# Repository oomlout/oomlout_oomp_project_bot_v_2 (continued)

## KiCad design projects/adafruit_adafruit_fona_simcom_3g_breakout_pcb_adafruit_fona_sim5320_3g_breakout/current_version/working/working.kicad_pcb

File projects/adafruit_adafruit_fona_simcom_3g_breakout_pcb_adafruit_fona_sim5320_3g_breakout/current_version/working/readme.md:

# adafruit_fona_simcom_3g_breakout_pcb
 
## summary 
* id: adafruit_adafruit_fona_simcom_3g_breakout_pcb_adafruit_fona_sim5320_3g_breakout
* user: adafruit
* name: adafruit_fona_simcom_3g_breakout_pcb
* board: adafruit_fona_sim5320_3g_breakout
* repo: https://github.com/adafruit/Adafruit-FONA-SIMCOM-3G-Breakout-PCB

* src_file_repo_sch: 
* src_file_repo_sch_link: https://github.com/adafruit/Adafruit-FONA-SIMCOM-3G-Breakout-PCB/tree/master/
* full details link: https://github.com/oomlout/oomlout_oomp_project_bot_v_2/tree/main/projects/adafruit_adafruit_fona_simcom_3g_breakout_pcb_adafruit_fona_sim5320_3g_breakout/current_version/working  

## schematic  
  
[schematic (pdf)](working_schematic.pdf) 

## pcb  

[board (pdf)](working.pdf)  

## working_bom
| Id | Designator | Footprint | Quantity | Designation | Supplier and ref |  | None | 
| --- | --- | --- | --- | --- | --- | --- | --- | 
| 1 | R2,R4,R5 | 0805-NO | 3 | 1K |  |  | [''] | 
| 2 | C15,C17 | RESPACK_4X0603 | 2 | 10pF |  |  | [''] | 
| 3 | IC1 | TSSOP14 | 1 | 74VHCT125PW |  |  | [''] | 
| 4 | D2 | SOT363 | 1 | SMF05C |  |  | [''] | 
| 5 | FID1,FID2,FID3,FID4,FID5 | FIDUCIAL_1MM | 5 | FIDUCIAL" |  |  | [''] | 
| 6 | U2 | SOT23-5 | 1 | MCP73831T-2ACI/OT |  |  | [''] | 
| 7 | Q2 | SOT23-WIDE | 1 | bss138 |  |  | [''] | 
| 8 | C14,C16 | RESPACK_4X0603 | 2 | 33pF |  |  | [''] | 
| 9 | D4,D5,D6,D3 | SOD-323 | 4 | 1N4148 |  |  | [''] | 
| 10 | C9,C11 | 0805-NO | 2 | 10uF |  |  | [''] | 
| 11 | R6,R3 | 0805-NO | 2 | 2K |  |  | [''] | 
| 12 | CHRG0 | CHIPLED_0805_NOOUTLINE | 1 | ORANGE |  |  | [''] | 
| 13 | JP1 | 1X18_ROUND70 | 1 |  |  |  | [''] | 
| 14 | GPSBIAS0 | SOLDERJUMPER_ARROW_NOPASTE | 1 |  |  |  | [''] | 
| 15 | CN2 | JSTPH2 | 1 | JSTPH |  |  | [''] | 
| 16 | C6,C4,C10,C3 | 0805-NO | 4 | 33pF |  |  | [''] | 
| 17 | C1 | 0805-NO | 1 | 10ÂµF |  |  | [''] | 
| 18 | C8,C5 | 0805-NO | 2 | 10pF |  |  | [''] | 
| 19 | X1 | SMA_EDGELAUNCH_UFL | 1 | uFL |  |  | [''] | 
| 20 | U$33,U$34 | MOUNTINGHOLE_2.5_PLATED | 2 | MOUNTINGHOLE2.5 |  |  | [''] | 
| 21 | U$21 | ADAFRUIT_2.5MM | 1 |  |  |  | [''] | 
| 22 | R1 | 0805-NO | 1 | 470 |  |  | [''] | 
| 23 | C2,C7 | C1210 | 2 | 100uF |  |  | [''] | 
| 24 | PWRSTAT0,DONE0 | CHIPLED_0805_NOOUTLINE | 2 | GREEN |  |  | [''] | 
| 25 | U1 | SIM5320 | 1 | SIM5320 |  |  | [''] | 
| 26 | X2 | 4UCONN_20329 | 1 | MicroB |  |  | [''] | 
| 27 | R8 | 0805-NO | 1 | 10K |  |  | [''] | 
| 28 | L2 | _0805MP | 1 | 33nH |  |  | [''] | 
| 29 | X3 | U.FL | 1 | uFL |  |  | [''] | 
| 30 | NETSTAT0 | CHIPLED_0805_NOOUTLINE | 1 | RED |  |  | [''] | 
| 31 | JP2 | 1X02_ROUND | 1 |  |  |  | [''] | 
| 32 | X4 | 4UCONN_18510 | 1 | 4UCONN_18510 |  |  | [''] | 
| 33 | D1 | SOD-123 | 1 | MMSZ5231BT1G |  |  | [''] | 
| 34 | SW1 | BTN_KMR2_4.6X2.8 | 1 | KMR2 |  |  | [''] | 
| 35 | U$42 | ADAFRUIT_TEXT_20MM | 1 |  |  |  | [''] | 
| 36 | U$25 | PCBFEAT-REV-040 | 1 |  |  |  | [''] | 
| 37 | TP1 | TP11R | 1 | TPTP11R |  |  | [''] | 
| 38 | U$36 | ADAFRUIT_5MM | 1 |  |  |  | [''] | 
| 39 | X6 | C707_10M006_512_2 | 1 | SIM_LOCKAMPHENOL |  |  | [''] | 
| 40 | U$26 | FONA_LOGO | 1 |  |  |  | [''] | 

## bom_schematic
| Ref | Qnty | Value | Cmp name | Footprint | Description | Vendor | DNP | 
| --- | --- | --- | --- | --- | --- | --- | --- | 
| C1 | 1 | 10ÂµF | CAP_CERAMIC0805-NOOUTLINE | working:0805-NO |  |  |  | 
| C2, C7 | 2 | 100uF | C-USC1210 | working:C1210 |  |  |  | 
| C3, C4, C6, C10 | 4 | 33pF | CAP_CERAMIC0805-NOOUTLINE | working:0805-NO |  |  |  | 
| C5, C8 | 2 | 10pF | CAP_CERAMIC0805-NOOUTLINE | working:0805-NO |  |  |  | 
| C9, C11 | 2 | 10uF | CAP_CERAMIC0805-NOOUTLINE | working:0805-NO |  |  |  | 
| C14, C16 | 2 | 33pF | CAP_4PACK1206 | working:RESPACK_4X0603 |  |  |  | 
| C15, C17 | 2 | 10pF | CAP_4PACK1206 | working:RESPACK_4X0603 |  |  |  | 
| CHRG0 | 1 | ORANGE | LED0805_NOOUTLINE | working:CHIPLED_0805_NOOUTLINE |  |  |  | 
| CN2 | 1 | JSTPH | JST_2PIN | working:JSTPH2 |  |  |  | 
| D1 | 1 | MMSZ5231BT1G | DIODE-ZENERSOD123 | working:SOD-123 |  |  |  | 
| D2 | 1 | SMF05C | TVSARRAY_5LANE | working:SOT363 |  |  |  | 
| D3, D4, D5, D6 | 4 | 1N4148 | DIODESOD-323 | working:SOD-323 |  |  |  | 
| DONE0 | 1 | GREEN | LED0805_NOOUTLINE | working:CHIPLED_0805_NOOUTLINE |  |  |  | 
| FID1, FID2, FID3, FID4, FID5 | 5 | FIDUCIAL"" | FIDUCIAL{dblquote}{dblquote} | working:FIDUCIAL_1MM |  |  |  | 
| GPSBIAS0 | 1 | SOLDERJUMPER | SOLDERJUMPER | working:SOLDERJUMPER_ARROW_NOPASTE |  |  |  | 
| IC1 | 1 | 74125PW | 74125PW | working:TSSOP14 |  |  |  | 
| JP1 | 1 | HEADER-1X18 | HEADER-1X18 | working:1X18_ROUND70 |  |  |  | 
| JP2 | 1 | HEADER-1X2ROUND | HEADER-1X2ROUND | working:1X02_ROUND |  |  |  | 
| L2 | 1 | 33nH | INDUCTOR_0805MP | working:_0805MP |  |  |  | 
| NETSTAT0 | 1 | RED | LED0805_NOOUTLINE | working:CHIPLED_0805_NOOUTLINE |  |  |  | 
| PWRSTAT0 | 1 | GREEN | LED0805_NOOUTLINE | working:CHIPLED_0805_NOOUTLINE |  |  |  | 
| Q2 | 1 | bss138 | MOSFET-NWIDE | working:SOT23-WIDE |  |  |  | 
| R1 | 1 | 470 | RESISTOR0805_NOOUTLINE | working:0805-NO |  |  |  | 
| R2, R4, R5 | 3 | 1K | RESISTOR0805_NOOUTLINE | working:0805-NO |  |  |  | 
| R3, R6 | 2 | 2K | RESISTOR0805_NOOUTLINE | working:0805-NO |  |  |  | 
| R8 | 1 | 10K | RESISTOR0805_NOOUTLINE | working:0805-NO |  |  |  | 
| SW1 | 1 | KMR2 | SWITCH_TACT_SMT4.6X2.8 | working:BTN_KMR2_4.6X2.8 |  |  |  | 
| TP1 | 1 | TPTP11R | TPTP11R | working:TP11R |  |  |  | 
| U1 | 1 | SIM5320 | GSM_SIM5320_LITERAL | working:SIM5320 |  |  |  | 
| U2 | 1 | MCP73831T-2ACI/OT | MCP73831/2 | working:SOT23-5 |  |  |  | 
| U$33, U$34 | 2 | MOUNTINGHOLE2.5 | MOUNTINGHOLE2.5 | working:MOUNTINGHOLE_2.5_PLATED |  |  |  | 
| X1 | 1 | uFL | SMACONNECTOR_EDGE_UFL | working:SMA_EDGELAUNCH_UFL |  |  |  | 
| X2 | 1 | MicroB | USBMICRO_20329 | working:4UCONN_20329 |  |  |  | 
| X3 | 1 | uFL | ANTENNA_U.FL | working:U.FL |  |  |  | 
| X4 | 1 | 4UCONN_18510 | AUDIO_3.5MMJACK_4POL | working:4UCONN_18510 |  |  |  | 
| X6 | 1 | SIM_LOCKAMPHENOL | SIM_LOCKAMPHENOL | working:C707_10M006_512_2 |  |  |  | 

## mounting_holes
| x | y | package | value | ref | size | 
| --- | --- | --- | --- | --- | --- | 
| 40.64 | 0.0 | MOUNTINGHOLE_2.5_PLATED | MOUNTINGHOLE2.5 | U$33 | m3 | 
| 0.0 | 0.0 | MOUNTINGHOLE_2.5_PLATED | MOUNTINGHOLE2.5 | U$34 | m3 |

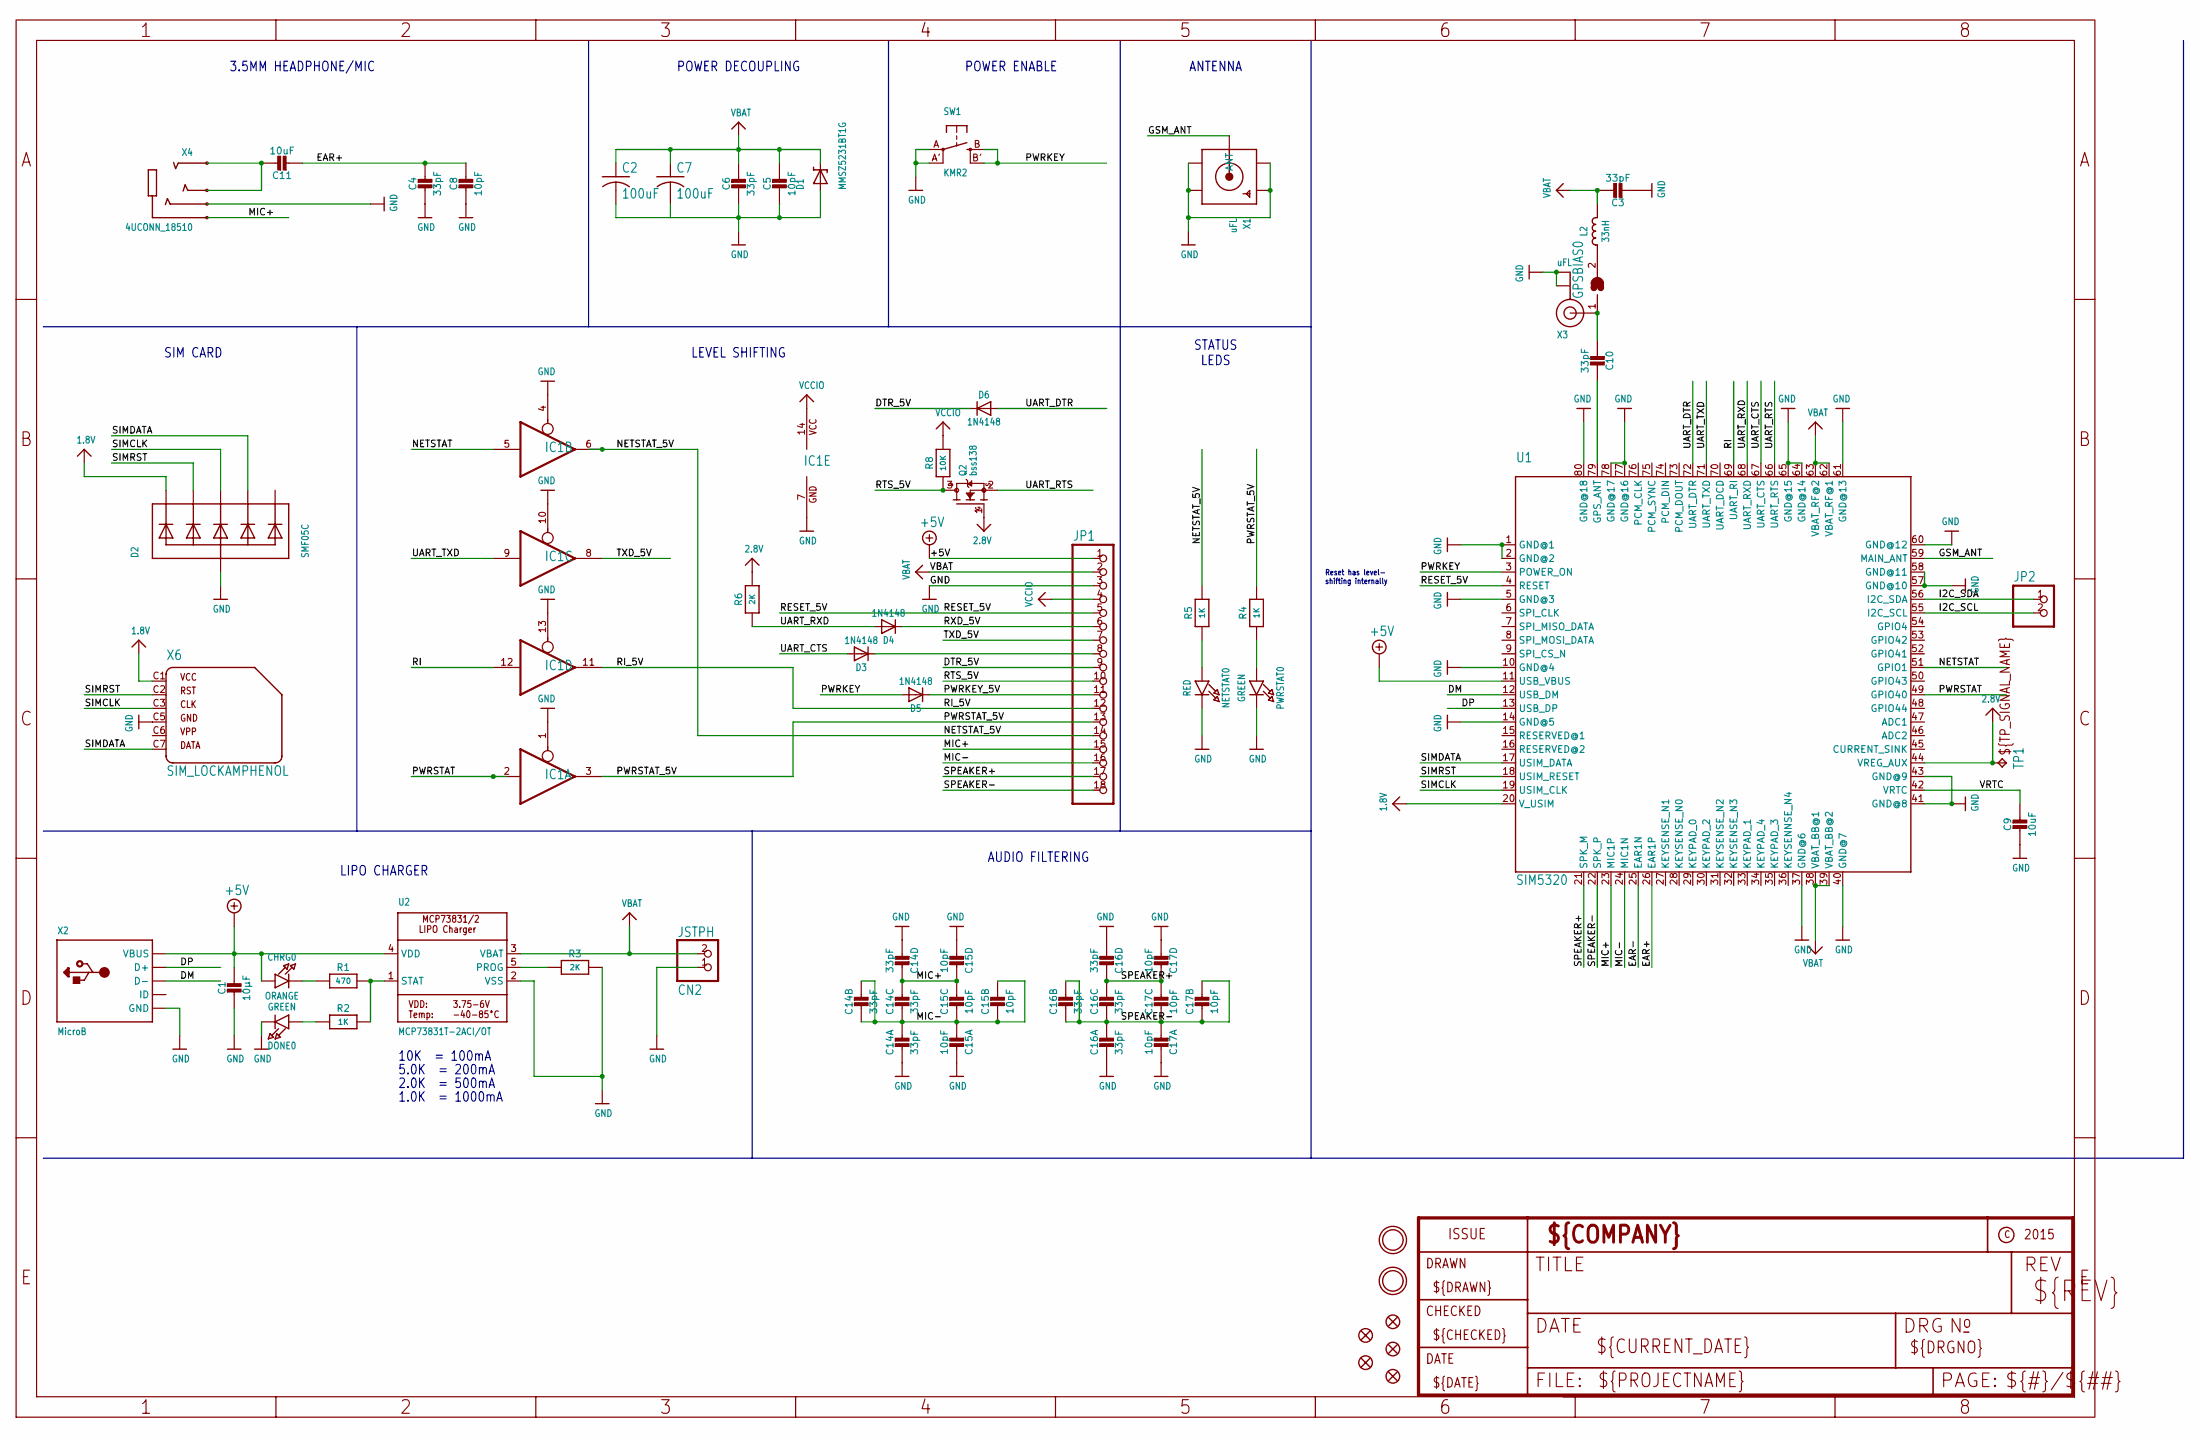
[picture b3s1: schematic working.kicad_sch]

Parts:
C1: 10µF; 0805-NO
C2, C7: 100uF; C1210
C3, C4, C6, C10: 33pF; 0805-NO
C5, C8: 10pF; 0805-NO
C9, C11: 10uF; 0805-NO
C14, C16: 33pF; RESPACK_4X0603
C15, C17: 10pF; RESPACK_4X0603
CHRG0: ORANGE; CHIPLED_0805_NOOUTLINE
CN2: JSTPH; JSTPH2
D1: MMSZ5231BT1G; SOD-123
D2: SMF05C; SOT363
D3, D4, D5, D6: 1N4148; SOD-323
DONE0: GREEN; CHIPLED_0805_NOOUTLINE
FID1, FID2, FID3, FID4, FID5: FIDUCIAL""; FIDUCIAL_1MM
GPSBIAS0: SOLDERJUMPER; SOLDERJUMPER_ARROW_NOPASTE
IC1: 74125PW; TSSOP14
JP1: HEADER-1X18; 1X18_ROUND70
JP2: HEADER-1X2ROUND; 1X02_ROUND
L2: 33nH; _0805MP
NETSTAT0: RED; CHIPLED_0805_NOOUTLINE
PWRSTAT0: GREEN; CHIPLED_0805_NOOUTLINE
Q2: bss138; SOT23-WIDE
R1: 470; 0805-NO
R2, R4, R5: 1K; 0805-NO
R3, R6: 2K; 0805-NO
R8: 10K; 0805-NO
SW1: KMR2; BTN_KMR2_4.6X2.8
TP1: TPTP11R; TP11R
U1: SIM5320
U2: MCP73831T-2ACI/OT; SOT23-5
U$33, U$34: MOUNTINGHOLE2.5; MOUNTINGHOLE_2.5_PLATED
X1: uFL; SMA_EDGELAUNCH_UFL
X2: MicroB; 4UCONN_20329
X3: uFL; U.FL
X4: 4UCONN_18510
X6: SIM_LOCKAMPHENOL; C707_10M006_512_2

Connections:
1.8V: D2.1 (C1), U1.20 (V_USIM), X6.C1 (1)
2.8V: Q2.1 (G), R6.2, TP1.TP, U1.44 (VREG_AUX)
+5V: C1.1, CHRG0.A, JP1.1, U1.11 (USB_VBUS), U2.4 (VDD), X2.VBUS
CTS_5V: D3.C, JP1.8
DM: U1.12 (USB_DM), X2.D-
DP: U1.13 (USB_DP), X2.D+
DTR_5V: D6.C, JP1.9
EAR+: C4.1, C8.1, C11.2, U1.26 (EAR1P)
EAR-: U1.25 (EAR1N)
GND: C1.2, C2.2, C3.2, C4.2, C5.2, C6.2, C7.2, C8.2, C9.2, C14.5 (2), C14.8 (2), C15.4 (1), C15.8 (2), C16.5 (2), C16.8 (2), C17.4 (1), C17.8 (2), CN2.1, D1.A, D2.2 (A), DONE0.C, IC1.1 (OE), IC1.4 (OE), IC1.7 (GND), IC1.10 (OE), IC1.13 (OE), JP1.3, NETSTAT0.C, PWRSTAT0.C, R3.2, SW1.A, SW1.A' (P1), U1.1 (GND@1), U1.2 (GND@2), U1.5 (GND@3), U1.10 (GND@4), U1.14 (GND@5), U1.37 (GND@6), U1.40 (GND@7), U1.41 (GND@8), U1.43 (GND@9), U1.57 (GND@10), U1.58 (GND@11), U1.60 (GND@12), U1.61 (GND@13), U1.64 (GND@14), U1.65 (GND@15), U1.77 (GND@16), U1.78 (GND@17), U1.80 (GND@18), U2.2 (VSS), X1.GND@1 (GND1), X1.GND@2 (GND2), X1.GND@3 (GND3), X1.GND@4 (GND4), X2.BASE@1 (GND), X2.BASE@2 (GND), X2.GND, X2.SPRT@1 (GND), X2.SPRT@2 (GND), X2.SPRT@3 (GND), X2.SPRT@4 (GND), X3.1 (GND@0), X3.2 (GND@1), X4.4-INNER_SLEEVE (RING1), X6.C5 (4)
GSM_ANT: U1.59 (MAIN_ANT), X1.P (ANT)
HP+: C11.1, X4.2-TIP (RING3), X4.3-OUTER_SLEEVE (RING2)
I2C_SCL: JP2.2, U1.55 (I2C_SCL)
I2C_SDA: JP2.1, U1.56 (I2C_SDA)
MIC+: C14.1, C14.2 (1), C15.1, C15.2 (1), JP1.15, U1.23 (MIC1P), X4.1-GND (TIP)
MIC-: C14.3 (1), C14.4 (1), C14.6 (2), C14.7 (2), C15.3 (1), C15.5 (2), C15.6 (2), C15.7 (2), JP1.16, U1.24 (MIC1N)
unnamed: CHRG0.C, R1.1
unnamed: R1.2, R2.2, U2.1 (STAT)
unnamed: C10.2, GPSBIAS0.1, X3.3 (SIGNAL)
unnamed: PWRSTAT0.A, R4.1
unnamed: R3.1, U2.5 (PROG)
unnamed: DONE0.A, R2.1
unnamed: C10.1, U1.79 (GPS_ANT)
unnamed: NETSTAT0.A, R5.1
unnamed: GPSBIAS0.2, L2.1
NETSTAT: IC1.5 (I), U1.51 (GPIO1)
NETSTAT_5V: IC1.6 (O), JP1.14, R5.2
PWRKEY: D5.A, SW1.B (S), SW1.B' (S1), U1.3 (POWER_ON)
PWRKEY_5V: D5.C, JP1.11
PWRSTAT: IC1.2 (I), U1.49 (GPIO40)
PWRSTAT_5V: IC1.3 (O), JP1.13, R4.2
RESET_5V: JP1.5, U1.4 (RESET)
RI: IC1.12 (I), U1.69 (UART_RI)
RI_5V: IC1.11 (O), JP1.12
RTS_5V: JP1.10, Q2.3 (D), R8.1
RXD_5V: D4.C, JP1.6
SIMCLK: D2.4 (C3), U1.19 (USIM_CLK), X6.C3 (3)
SIMDATA: D2.5 (C4), U1.17 (USIM_DATA), X6.C7 (6)
SIMRST: D2.3 (C2), U1.18 (USIM_RESET), X6.C2 (2)
SPEAKER+: C16.1, C16.2 (1), C17.1, C17.2 (1), JP1.17, U1.21 (SPK_M)
SPEAKER-: C16.3 (1), C16.4 (1), C16.6 (2), C16.7 (2), C17.3 (1), C17.5 (2), C17.6 (2), C17.7 (2), JP1.18, U1.22 (SPK_P)
TXD_5V: IC1.8 (O), JP1.7
UART_CTS: D3.A, U1.67 (UART_CTS)
UART_DTR: D6.A, U1.72 (UART_DTR)
UART_RTS: Q2.2 (S), U1.66 (UART_RTS)
UART_RXD: D4.A, R6.1, U1.68 (UART_RXD)
UART_TXD: IC1.9 (I), U1.71 (UART_TXD)
VBAT: C2.1, C3.1, C5.1, C6.1, C7.1, CN2.2, D1.C, JP1.2, L2.2, U1.38 (VBAT_BB@1), U1.39 (VBAT_BB@2), U1.62 (VBAT_RF@1), U1.63 (VBAT_RF@2), U2.3 (VBAT)
VCCIO: IC1.14 (VCC), JP1.4, R8.2
VRTC: C9.1, U1.42 (VRTC)

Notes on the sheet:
STATUS LEDS
2.0K = 500mA
SIM CARD
ANTENNA
LEVEL SHIFTING
LIPO CHARGER
Reset has level- shifting internally
POWER ENABLE
1.0K = 1000mA
AUDIO FILTERING
POWER DECOUPLING
3.5MM HEADPHONE/MIC
10K = 100mA
5.0K = 200mA

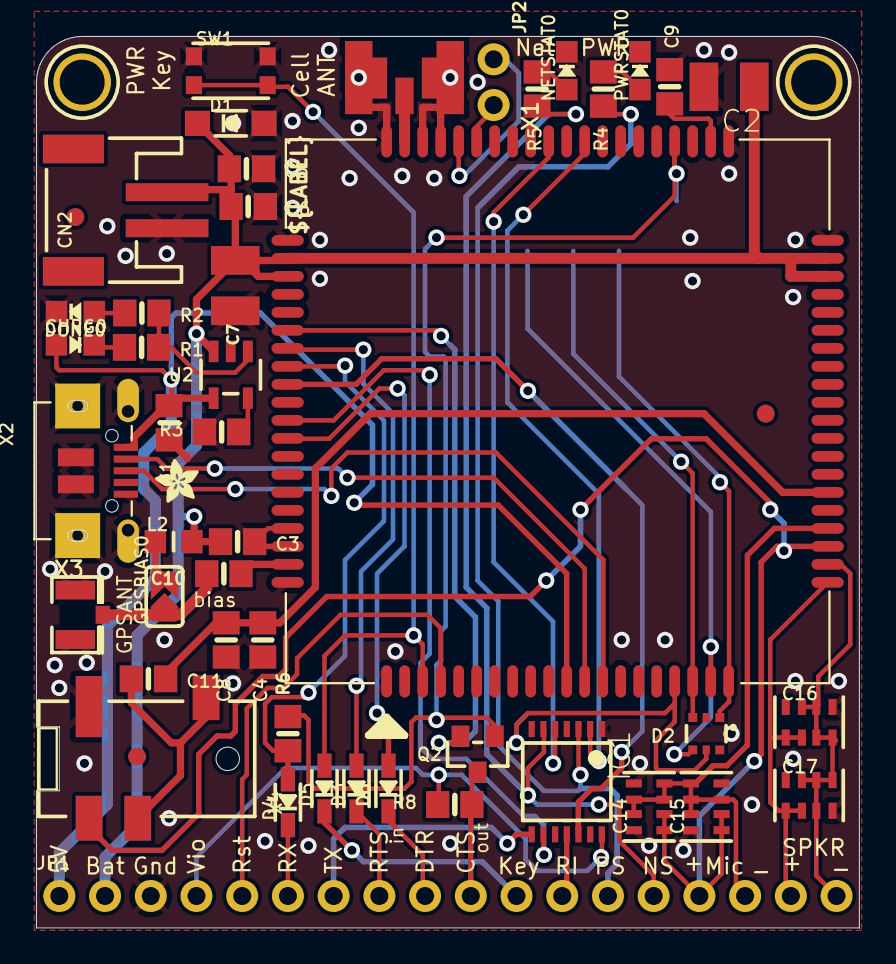
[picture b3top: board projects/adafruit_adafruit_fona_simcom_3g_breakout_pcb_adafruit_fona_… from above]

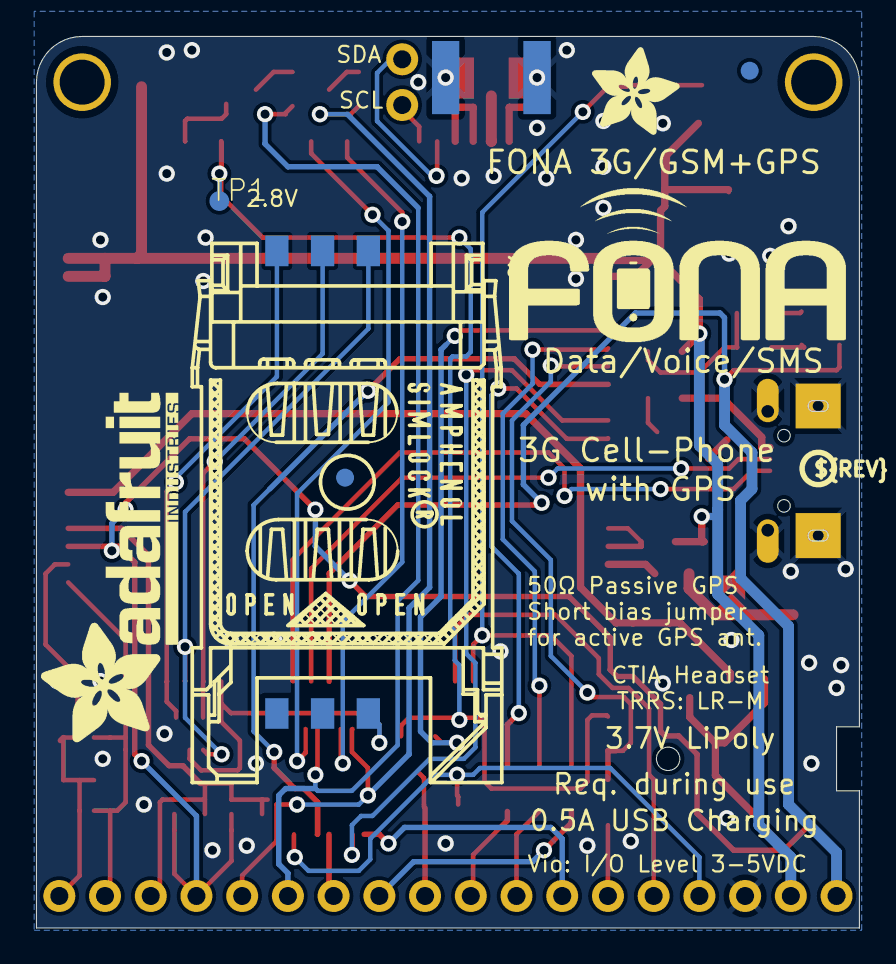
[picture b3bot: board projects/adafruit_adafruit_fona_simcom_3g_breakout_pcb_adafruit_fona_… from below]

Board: 2 copper layers, 45.7 x 49.5 mm, 60 parts (8 on the bottom side), 49 nets.

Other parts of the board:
U$21: ADAFRUIT_2.5MM
U$25: PCBFEAT-REV-040
U$26: FONA_LOGO
U$36: ADAFRUIT_5MM
U$42: ADAFRUIT_TEXT_20MM

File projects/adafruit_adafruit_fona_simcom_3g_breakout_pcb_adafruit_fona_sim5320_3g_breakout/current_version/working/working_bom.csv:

"Id";"Designator";"Footprint";"Quantity";"Designation";"Supplier and ref";
1;"R2,R4,R5";"0805-NO";3;"1K";;;
2;"C15,C17";"RESPACK_4X0603";2;"10pF";;;
3;"IC1";"TSSOP14";1;"74VHCT125PW";;;
4;"D2";"SOT363";1;"SMF05C";;;
5;"FID1,FID2,FID3,FID4,FID5";"FIDUCIAL_1MM";5;"FIDUCIAL""";;;
6;"U2";"SOT23-5";1;"MCP73831T-2ACI/OT";;;
7;"Q2";"SOT23-WIDE";1;"bss138";;;
8;"C14,C16";"RESPACK_4X0603";2;"33pF";;;
9;"D4,D5,D6,D3";"SOD-323";4;"1N4148";;;
10;"C9,C11";"0805-NO";2;"10uF";;;
11;"R6,R3";"0805-NO";2;"2K";;;
12;"CHRG0";"CHIPLED_0805_NOOUTLINE";1;"ORANGE";;;
13;"JP1";"1X18_ROUND70";1;"";;;
14;"GPSBIAS0";"SOLDERJUMPER_ARROW_NOPASTE";1;"";;;
15;"CN2";"JSTPH2";1;"JSTPH";;;
16;"C6,C4,C10,C3";"0805-NO";4;"33pF";;;
17;"C1";"0805-NO";1;"10µF";;;
18;"C8,C5";"0805-NO";2;"10pF";;;
19;"X1";"SMA_EDGELAUNCH_UFL";1;"uFL";;;
20;"U$33,U$34";"MOUNTINGHOLE_2.5_PLATED";2;"MOUNTINGHOLE2.5";;;
21;"U$21";"ADAFRUIT_2.5MM";1;"";;;
22;"R1";"0805-NO";1;"470";;;
23;"C2,C7";"C1210";2;"100uF";;;
24;"PWRSTAT0,DONE0";"CHIPLED_0805_NOOUTLINE";2;"GREEN";;;
25;"U1";"SIM5320";1;"SIM5320";;;
26;"X2";"4UCONN_20329";1;"MicroB";;;
27;"R8";"0805-NO";1;"10K";;;
28;"L2";"_0805MP";1;"33nH";;;
29;"X3";"U.FL";1;"uFL";;;
30;"NETSTAT0";"CHIPLED_0805_NOOUTLINE";1;"RED";;;
31;"JP2";"1X02_ROUND";1;"";;;
32;"X4";"4UCONN_18510";1;"4UCONN_18510";;;
33;"D1";"SOD-123";1;"MMSZ5231BT1G";;;
34;"SW1";"BTN_KMR2_4.6X2.8";1;"KMR2";;;
35;"U$42";"ADAFRUIT_TEXT_20MM";1;"";;;
36;"U$25";"PCBFEAT-REV-040";1;"";;;
37;"TP1";"TP11R";1;"TPTP11R";;;
38;"U$36";"ADAFRUIT_5MM";1;"";;;
39;"X6";"C707_10M006_512_2";1;"SIM_LOCKAMPHENOL";;;
40;"U$26";"FONA_LOGO";1;"";;;

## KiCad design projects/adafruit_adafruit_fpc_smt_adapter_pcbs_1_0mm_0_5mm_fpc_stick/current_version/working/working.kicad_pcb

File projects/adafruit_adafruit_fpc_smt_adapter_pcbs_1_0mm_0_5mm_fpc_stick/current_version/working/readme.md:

# adafruit_fpc_smt_adapter_pcbs
 
## summary 
* id: adafruit_adafruit_fpc_smt_adapter_pcbs_1_0mm_0_5mm_fpc_stick
* user: adafruit
* name: adafruit_fpc_smt_adapter_pcbs
* board: 1_0mm_0_5mm_fpc_stick
* repo: https://github.com/adafruit/Adafruit-FPC-SMT-Adapter-PCBs

* src_file_repo_sch: 
* src_file_repo_sch_link: https://github.com/adafruit/Adafruit-FPC-SMT-Adapter-PCBs/tree/master/
* full details link: https://github.com/oomlout/oomlout_oomp_project_bot_v_2/tree/main/projects/adafruit_adafruit_fpc_smt_adapter_pcbs_1_0mm_0_5mm_fpc_stick/current_version/working  

## schematic  
  
[schematic (pdf)](working_schematic.pdf) 

## pcb  

[board (pdf)](working.pdf)  

## working_bom
| Id | Designator | Footprint | Quantity | Designation | Supplier and ref |  | None | 
| --- | --- | --- | --- | --- | --- | --- | --- | 
| 1 | JP2 | 1X20_ROUND | 1 |  |  |  | [''] | 
| 2 | @HOLE0,@HOLE1 |  | 2 |  |  |  | [''] | 
| 3 | U$2,U$3 | ADAFRUIT_5MM | 2 |  |  |  | [''] | 
| 4 | JP1 | FPC_GENERIC_1.0MM_20PIN | 1 |  |  |  | [''] | 
| 5 | JP3 | FPC_GENERIC_0.5MM_20PIN | 1 |  |  |  | [''] | 

## bom_schematic
| Ref | Qnty | Value | Cmp name | Footprint | Description | Vendor | DNP | 
| --- | --- | --- | --- | --- | --- | --- | --- | 
| JP1 | 1 | HEADER-1X20FPC_1.0MM | HEADER-1X20FPC_1.0MM | working:FPC_GENERIC_1.0MM_20PIN |  |  |  | 
| JP2 | 1 | HEADER-1X20ROUND | HEADER-1X20ROUND | working:1X20_ROUND |  |  |  | 
| JP3 | 1 | HEADER-1X20FPC_0.5MM | HEADER-1X20FPC_0.5MM | working:FPC_GENERIC_0.5MM_20PIN |  |  |  |

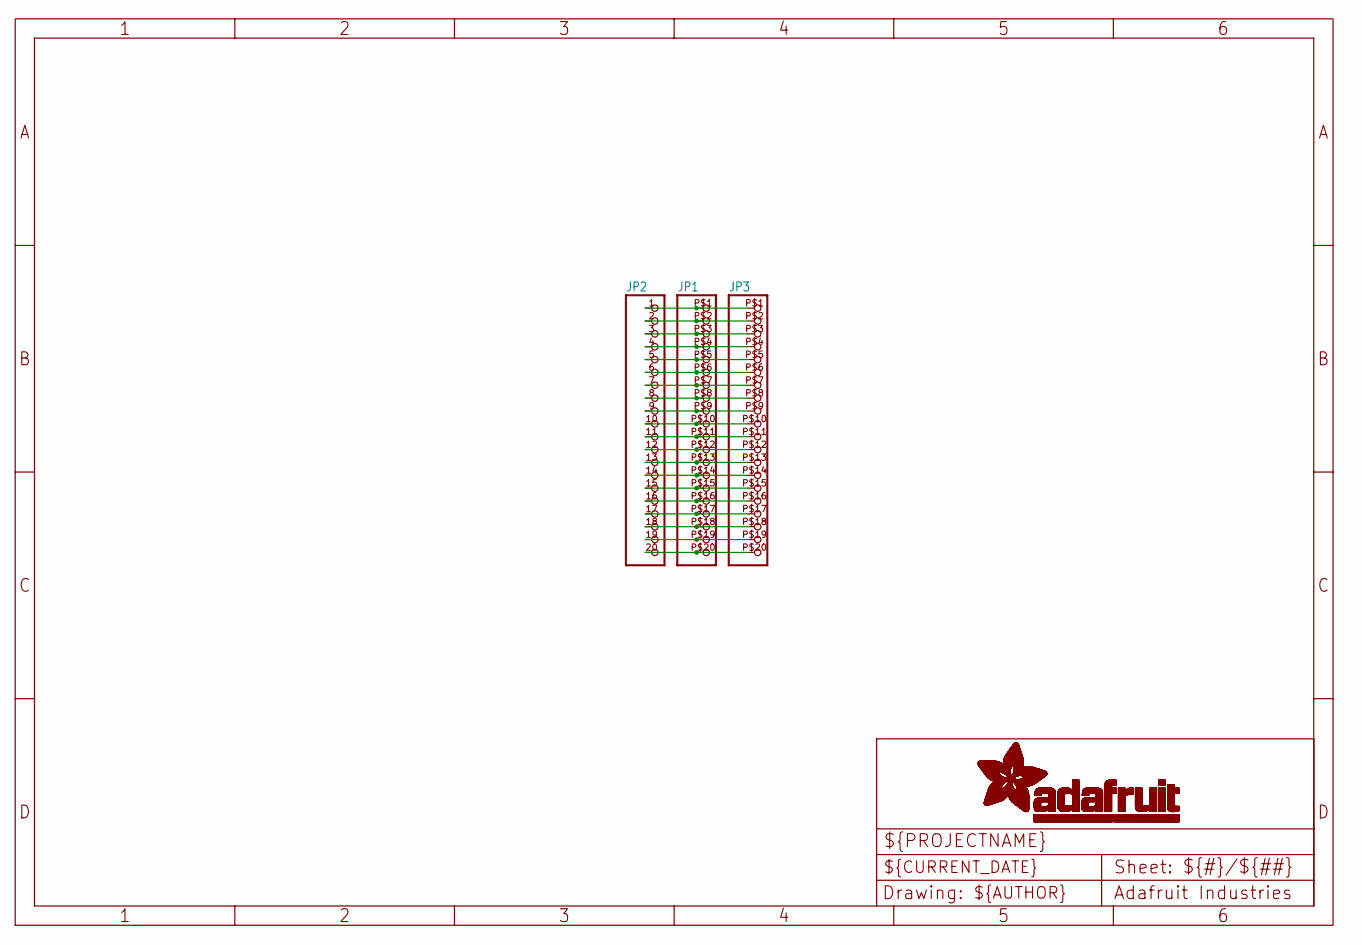
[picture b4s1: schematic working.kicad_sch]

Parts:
JP1: HEADER-1X20FPC_1.0MM; FPC_GENERIC_1.0MM_20PIN
JP2: HEADER-1X20ROUND; 1X20_ROUND
JP3: HEADER-1X20FPC_0.5MM; FPC_GENERIC_0.5MM_20PIN

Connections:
unnamed: JP1.P$1 (1), JP2.1, JP3.P$1 (1)
unnamed: JP1.P$2 (2), JP2.2, JP3.P$2 (2)
unnamed: JP1.P$3 (3), JP2.3, JP3.P$3 (3)
unnamed: JP1.P$4 (4), JP2.4, JP3.P$4 (4)
unnamed: JP1.P$5 (5), JP2.5, JP3.P$5 (5)
unnamed: JP1.P$6 (6), JP2.6, JP3.P$6 (6)
unnamed: JP1.P$7 (7), JP2.7, JP3.P$7 (7)
unnamed: JP1.P$8 (8), JP2.8, JP3.P$8 (8)
unnamed: JP1.P$9 (9), JP2.9, JP3.P$9 (9)
unnamed: JP1.P$10 (10), JP2.10, JP3.P$10 (10)
unnamed: JP1.P$11 (11), JP2.11, JP3.P$11 (11)
unnamed: JP1.P$12 (12), JP2.12, JP3.P$12 (12)
unnamed: JP1.P$13 (13), JP2.13, JP3.P$13 (13)
unnamed: JP1.P$14 (14), JP2.14, JP3.P$14 (14)
unnamed: JP1.P$15 (15), JP2.15, JP3.P$15 (15)
unnamed: JP1.P$16 (16), JP2.16, JP3.P$16 (16)
unnamed: JP1.P$17 (17), JP2.17, JP3.P$17 (17)
unnamed: JP1.P$18 (18), JP2.18, JP3.P$18 (18)
unnamed: JP1.P$19 (19), JP2.19, JP3.P$19 (19)
unnamed: JP1.P$20 (20), JP2.20, JP3.P$20 (20)

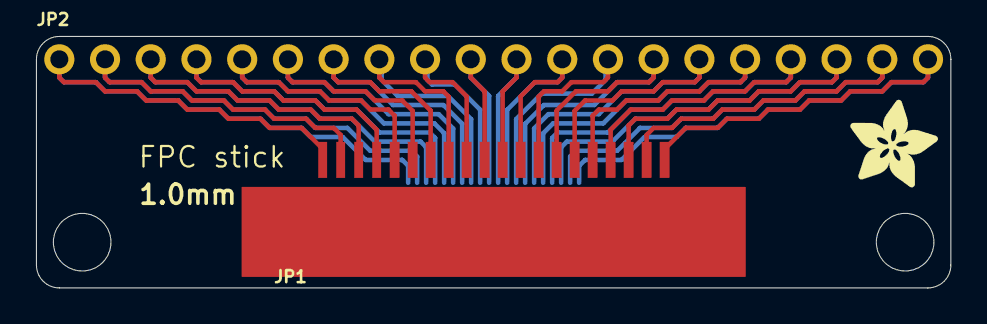
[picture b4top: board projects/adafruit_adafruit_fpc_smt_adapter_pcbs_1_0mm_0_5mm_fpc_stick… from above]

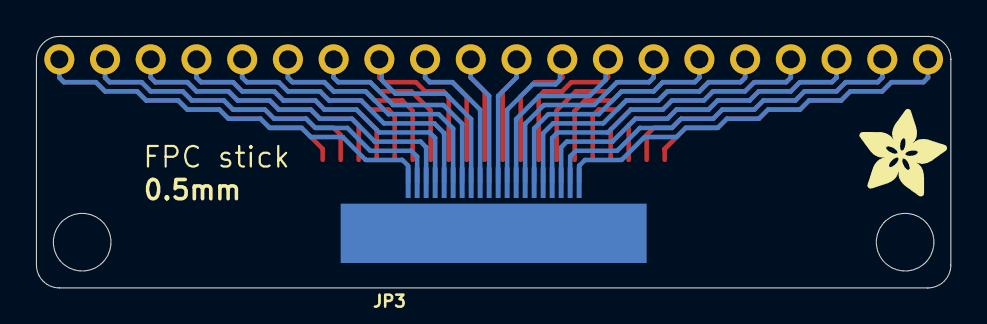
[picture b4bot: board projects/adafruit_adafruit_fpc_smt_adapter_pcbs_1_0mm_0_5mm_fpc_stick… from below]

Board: 2 copper layers, 50.8 x 14.0 mm, 7 parts (2 on the bottom side), 20 nets.

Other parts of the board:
@HOLE0, @HOLE1: (no value)
U$2, U$3: ADAFRUIT_5MM

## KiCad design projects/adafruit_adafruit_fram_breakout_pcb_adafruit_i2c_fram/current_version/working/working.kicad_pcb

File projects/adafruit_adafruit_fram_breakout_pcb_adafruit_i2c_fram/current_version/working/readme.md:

# adafruit_fram_breakout_pcb
 
## summary 
* id: adafruit_adafruit_fram_breakout_pcb_adafruit_i2c_fram
* user: adafruit
* name: adafruit_fram_breakout_pcb
* board: adafruit_i2c_fram
* repo: https://github.com/adafruit/Adafruit-FRAM-Breakout-PCB

* src_file_repo_sch: 
* src_file_repo_sch_link: https://github.com/adafruit/Adafruit-FRAM-Breakout-PCB/tree/master/
* full details link: https://github.com/oomlout/oomlout_oomp_project_bot_v_2/tree/main/projects/adafruit_adafruit_fram_breakout_pcb_adafruit_i2c_fram/current_version/working  

## schematic  
  
[schematic (pdf)](working_schematic.pdf) 

## pcb  

[board (pdf)](working.pdf)  

## working_bom
| Id | Designator | Footprint | Quantity | Designation | Supplier and ref |  | None | 
| --- | --- | --- | --- | --- | --- | --- | --- | 
| 1 | U$4 | ADAFRUIT_3.5MM | 1 |  |  |  | [''] | 
| 2 | FID1,FID2 | FIDUCIAL_1MM | 2 | FIDUCIAL" |  |  | [''] | 
| 3 | U1 | SOIC8_208MIL | 1 | MB85RC256VPF-G-JNERE2 |  |  | [''] | 
| 4 | U$6,U$5 | MOUNTINGHOLE_2.5_PLATED | 2 | MOUNTINGHOLE2.5 |  |  | [''] | 
| 5 | JP1 | 1X08_ROUND_70 | 1 |  |  |  | [''] | 
| 6 | R2,R1 | _0805MP | 2 | 10K |  |  | [''] | 
| 7 | C1 | _0805MP | 1 | 10uF |  |  | [''] | 

## bom_schematic
| Ref | Qnty | Value | Cmp name | Footprint | Description | Vendor | DNP | 
| --- | --- | --- | --- | --- | --- | --- | --- | 
| C1 | 1 | 10uF | CAP_CERAMIC_0805MP | working:_0805MP |  |  |  | 
| FID1, FID2 | 2 | FIDUCIAL"" | FIDUCIAL{dblquote}{dblquote} | working:FIDUCIAL_1MM |  |  |  | 
| JP1 | 1 | HEADER-1X870MIL | HEADER-1X870MIL | working:1X08_ROUND_70 |  |  |  | 
| R1, R2 | 2 | 10K | RESISTOR_0805MP | working:_0805MP |  |  |  | 
| U1 | 1 | MB85RC256VPF-G-JNERE2 | FRAM_SOIC8_I2C | working:SOIC8_208MIL |  |  |  | 
| U$5, U$6 | 2 | MOUNTINGHOLE2.5 | MOUNTINGHOLE2.5 | working:MOUNTINGHOLE_2.5_PLATED |  |  |  | 

## mounting_holes
| x | y | package | value | ref | size | 
| --- | --- | --- | --- | --- | --- | 
| 0.0 | 0.0 | MOUNTINGHOLE_2.5_PLATED | MOUNTINGHOLE2.5 | U$5 | m3 | 
| 15.24 | 0.0 | MOUNTINGHOLE_2.5_PLATED | MOUNTINGHOLE2.5 | U$6 | m3 |

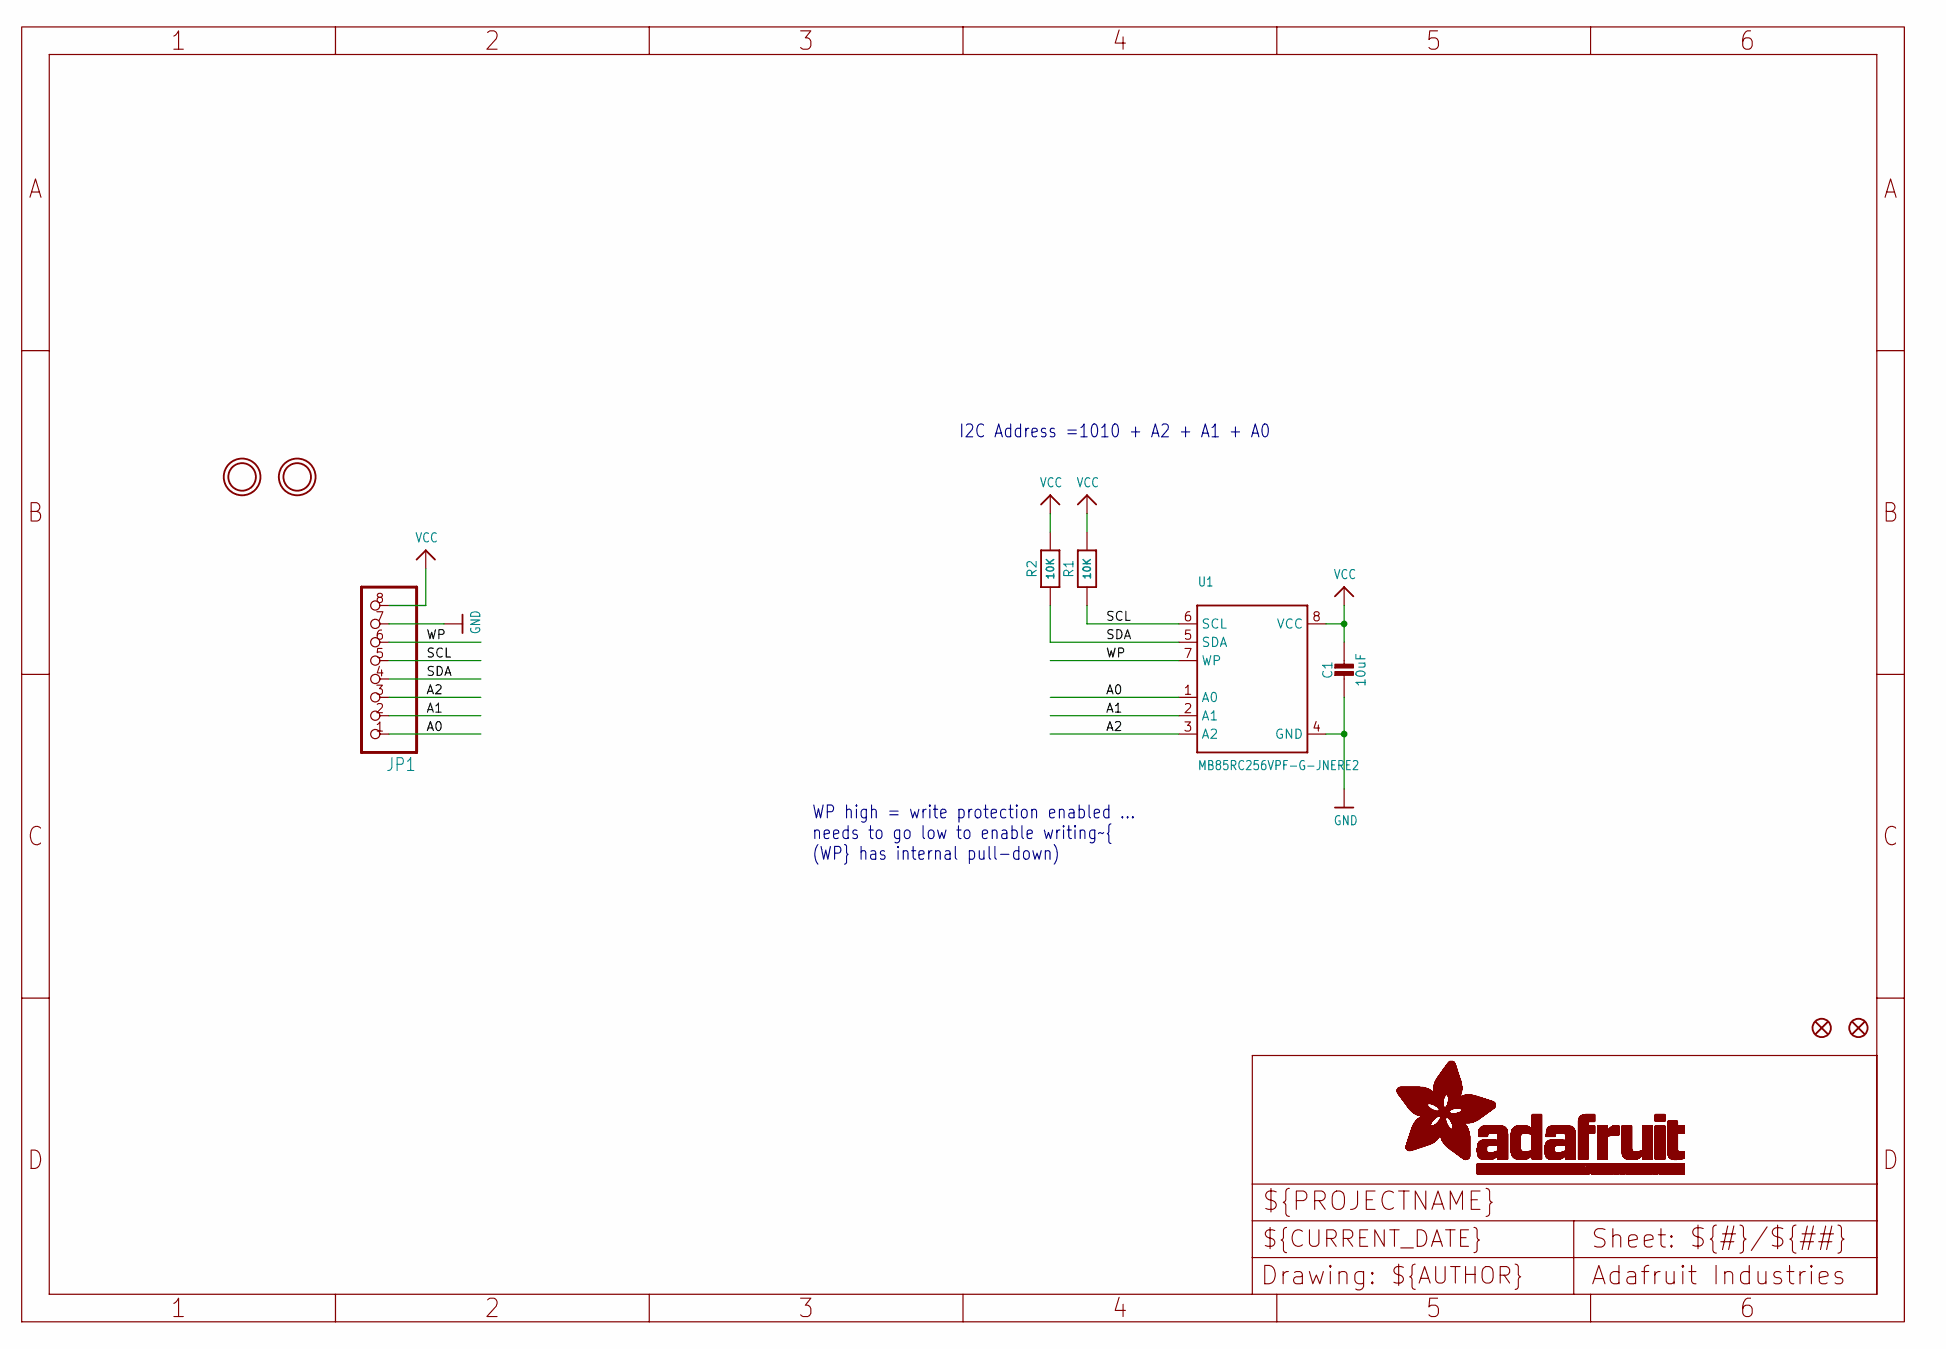
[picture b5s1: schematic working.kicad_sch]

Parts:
C1: 10uF; _0805MP
FID1, FID2: FIDUCIAL""; FIDUCIAL_1MM
JP1: HEADER-1X870MIL; 1X08_ROUND_70
R1, R2: 10K; _0805MP
U1: MB85RC256VPF-G-JNERE2; SOIC8_208MIL
U$5, U$6: MOUNTINGHOLE2.5; MOUNTINGHOLE_2.5_PLATED

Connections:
A0: JP1.1, U1.1 (A0)
A1: JP1.2, U1.2 (A1)
A2: JP1.3, U1.3 (A2)
GND: C1.2, JP1.7, U1.4 (GND)
SCL: JP1.5, R1.1, U1.6 (SCL)
SDA: JP1.4, R2.1, U1.5 (SDA)
VCC: C1.1, JP1.8, R1.2, R2.2, U1.8 (VCC)
WP: JP1.6, U1.7 (WP)

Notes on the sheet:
I2C Address =1010 + A2 + A1 + A0
WP high = write protection enabled ... needs to go low to enable writing~{ (WP} has internal pull-down)

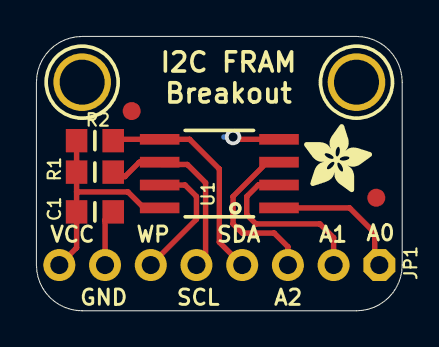
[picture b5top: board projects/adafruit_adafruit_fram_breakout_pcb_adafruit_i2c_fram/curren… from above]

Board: 2 copper layers, 20.3 x 15.2 mm, 10 parts (0 on the bottom side), 8 nets.

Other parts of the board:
U$4: ADAFRUIT_3.5MM
